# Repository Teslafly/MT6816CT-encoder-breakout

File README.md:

# MT6816CT-encoder-breakout
MT6816CT encoder breakout for vesc

Operates in 3 wire mode, may need to program encoder to get it to work.

Currently vesc only supports 4 wire for MT6816CT.

Todo:
* Add 3 wire transfer support to vesc
* Find out if sensotr needs programming to work in 3 wire mode
	* I can probably blindly write to sensor on startup to put into 3 wire mode. Since MOSI pin connected.
* Add bom with part links
* add pictures
	* KiCad renders
	* top/bottom of board
	* 4 connector configurtations
	* mounted to motor
* add 3d printed mount/standoff stl/cad
* add connecting cable bom / pics
	* 6 pair wire source, jst gh/ph crimps/housings, 
	* temp sensors & 2 pin crimp/housings

Made with KiCad nightly:
Version: (5.99.0-11535-gf6cac49802)

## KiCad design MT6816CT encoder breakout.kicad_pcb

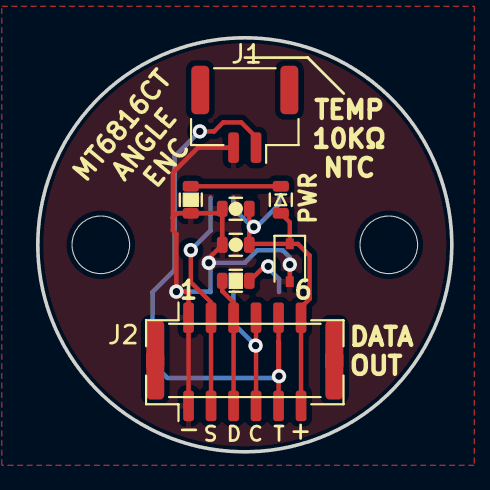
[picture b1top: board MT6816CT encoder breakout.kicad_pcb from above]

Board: 2 copper layers, 23.0 x 23.0 mm, 12 parts (1 on the bottom side), 8 nets.

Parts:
C1: 1uf; C_0603
C2: 4.7uf; C_0603
D1: GREEN LED; D_0603
D2: SD05-01FTG; D_SOD-323
H1, H2: MountingHole; MountingHole_3.2mm_M3
J1: Conn_01x02; JST_GH_SM02B-GHS-TB_1x02-1MP_P1.25mm_Horizontal
J2: Conn_01x06; JST_GH_BM06B-GHS-TBT_1x06-1MP_P1.25mm_Vertical
J3: Conn_01x06; JST_GH_SM06B-GHS-TB_1x06-1MP_P1.25mm_Horizontal
R1: 10k; R_0603
R2: 470R; R_0603
U2: MT6816CT; SOP-8_3.9x4.9mm_P1.27mm

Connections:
+5V: C1.1, C2.1, D1.A, D2.1 (K), J2.6, J3.6, U2.2 (HVPP/SPI_EN), U2.4 (VDD)
/H1/SCK: J2.4, J3.4, U2.7 (SCK/Z/W)
/H2/SSC_DATA: J2.3, J3.3, R2.1
/H3/CS: J2.2, J3.2, U2.1 (CSN)
/SDAT_R: R2.2, U2.5 (MOSI/SDAT/A/U)
/Temp: J1.1, J2.5, J3.5
GND: C1.2, C2.2, D2.2 (A), J1.2, J2.1, J3.1, R1.2, U2.8 (GND)
unnamed: D1.C (K), R1.1

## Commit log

2021-07-28 Added v1 of mt6816 based hall encoder board. made with kicad 5.99
